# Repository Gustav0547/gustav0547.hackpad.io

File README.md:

# gustav0547.hackpad.io
# Jason's Hackpad

Macropad with 16 buttons, 15 to run shortcuts, 1 to swap between sets of keys, and a screen to display what set of keys is active.

## [Bottom Case](https://github.com/Gustav0547/gustav0547.hackpad.io/blob/4d3d6c4bc20b1932a387ed43a1a903aacc122e63/cad/Hackpad%20Case%20V1.step)

.png)
Bottom Case with PCB

Full Assembly

## [Top Case](https://github.com/Gustav0547/gustav0547.hackpad.io/blob/4d3d6c4bc20b1932a387ed43a1a903aacc122e63/cad/Hackpad%20Case%20Top%20V2.step)

.png)

## [PCB File](https://github.com/Gustav0547/gustav0547.hackpad.io/blob/4d3d6c4bc20b1932a387ed43a1a903aacc122e63/kicad/Jason's%20Hackpad.kicad_pcb)

.png)

## [Schematic](https://github.com/Gustav0547/gustav0547.hackpad.io/blob/4d3d6c4bc20b1932a387ed43a1a903aacc122e63/kicad/Jason's%20Hackpad.kicad_sch)

.png)

## Files
- Cad:
    - [Bottom Case](https://github.com/Gustav0547/gustav0547.hackpad.io/blob/main/cad/Hackpad%20Case%20V1.step)
    - [Top Case](https://github.com/Gustav0547/gustav0547.hackpad.io/blob/main/cad/Hackpad%20Case%20Top%20V2.step)
- KiCad:
    - [Schematic](https://github.com/Gustav0547/gustav0547.hackpad.io/blob/4d3d6c4bc20b1932a387ed43a1a903aacc122e63/kicad/Jason's%20Hackpad.kicad_sch)
    - [PCB File](https://github.com/Gustav0547/gustav0547.hackpad.io/blob/4d3d6c4bc20b1932a387ed43a1a903aacc122e63/kicad/Jason's%20Hackpad.kicad_pcb)
    - [PRL File](https://github.com/Gustav0547/gustav0547.hackpad.io/blob/4d3d6c4bc20b1932a387ed43a1a903aacc122e63/kicad/Jason's%20Hackpad.kicad_prl)
    - [PRO File](https://github.com/Gustav0547/gustav0547.hackpad.io/blob/4d3d6c4bc20b1932a387ed43a1a903aacc122e63/kicad/Jason's%20Hackpad.kicad_pro)

## [Bill of Materials](https://github.com/Gustav0547/gustav0547.hackpad.io/blob/8d4ffa0d519144a892c286018dd9fab355bb3349/kicad/Jason's%20Hackpad.csv)
- 16 1N4148 Diodes
- 16 MX Style Switches
- 16 Blank DSA Keycaps
- 1 Speeed XIAO RP2040
- 1 0.91" OLED Display
- 4 M3x16mm Screws
- 4 M3 Heatset Inserts

## Features
- 16 Buttons in a matrix
    - 15 for macro keys
    - 1 to switch sets of active macro keys
- 0.91" OLED Display to show active keyset
- Diodes to prevent ghosting
- XIAO-RP2040 microcontroller
- 3D printed enclosure

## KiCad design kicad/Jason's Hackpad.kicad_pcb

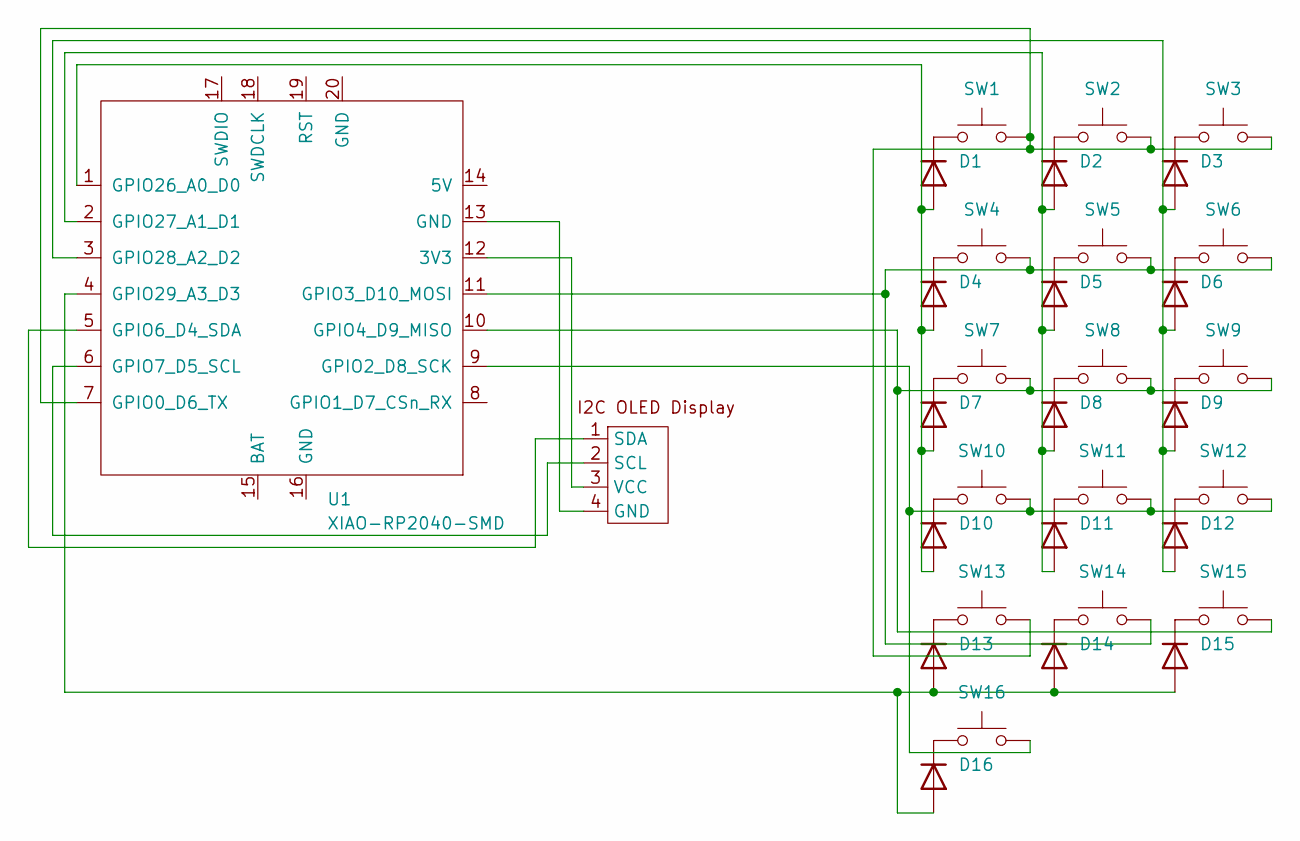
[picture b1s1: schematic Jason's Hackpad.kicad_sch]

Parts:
D1, D2, D3, D4, D5, D6, D7, D8, D9, D10, D11, D12, D13, D14, D15, D16: 1N4148; D_DO-35_SOD27_P7.62mm_Horizontal
SW1, SW2, SW3, SW4, SW5, SW6, SW7, SW8, SW9, SW10, SW11, SW12, SW13, SW14, SW15, SW16: SW_Push; SW_Cherry_MX_1.00u_PCB
U1: XIAO-RP2040-SMD; XIAO-RP2040-DIP
U2: Untitled

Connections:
unnamed: D1.2 (A), D4.2 (A), D7.2 (A), D10.2 (A), U1.1 (GPIO26_A0_D0)
unnamed: D1.1 (K), SW1.1
unnamed: D2.1 (K), SW2.1
unnamed: D3.1 (K), SW3.1
unnamed: D4.1 (K), SW4.1
unnamed: D5.1 (K), SW5.1
unnamed: D6.1 (K), SW6.1
unnamed: D7.1 (K), SW7.1
unnamed: D8.1 (K), SW8.1
unnamed: D9.1 (K), SW9.1
unnamed: D10.1 (K), SW10.1
unnamed: D2.2 (A), D5.2 (A), D8.2 (A), D11.2 (A), U1.2 (GPIO27_A1_D1)
unnamed: D11.1 (K), SW11.1
unnamed: D3.2 (A), D6.2 (A), D9.2 (A), D12.2 (A), U1.3 (GPIO28_A2_D2)
unnamed: D12.1 (K), SW12.1
unnamed: D13.2 (A), D14.2 (A), D15.2 (A), D16.2 (A), U1.4 (GPIO29_A3_D3)
unnamed: D13.1 (K), SW13.1
unnamed: D14.1 (K), SW14.1
unnamed: D15.1 (K), SW15.1
unnamed: D16.1 (K), SW16.1
unnamed: U1.12 (3V3), U2.3 (VCC)
unnamed: SW1.2, SW2.2, SW3.2, SW13.2, U1.7 (GPIO0_D6_TX)
unnamed: SW10.2, SW11.2, SW12.2, SW16.2, U1.9 (GPIO2_D8_SCK)
unnamed: SW4.2, SW5.2, SW6.2, SW14.2, U1.11 (GPIO3_D10_MOSI)
unnamed: SW7.2, SW8.2, SW9.2, SW15.2, U1.10 (GPIO4_D9_MISO)
unnamed: U1.5 (GPIO6_D4_SDA), U2.1 (SDA)
unnamed: U1.6 (GPIO7_D5_SCL), U2.2 (SCL)
unnamed: U1.13 (GND), U2.4 (GND)

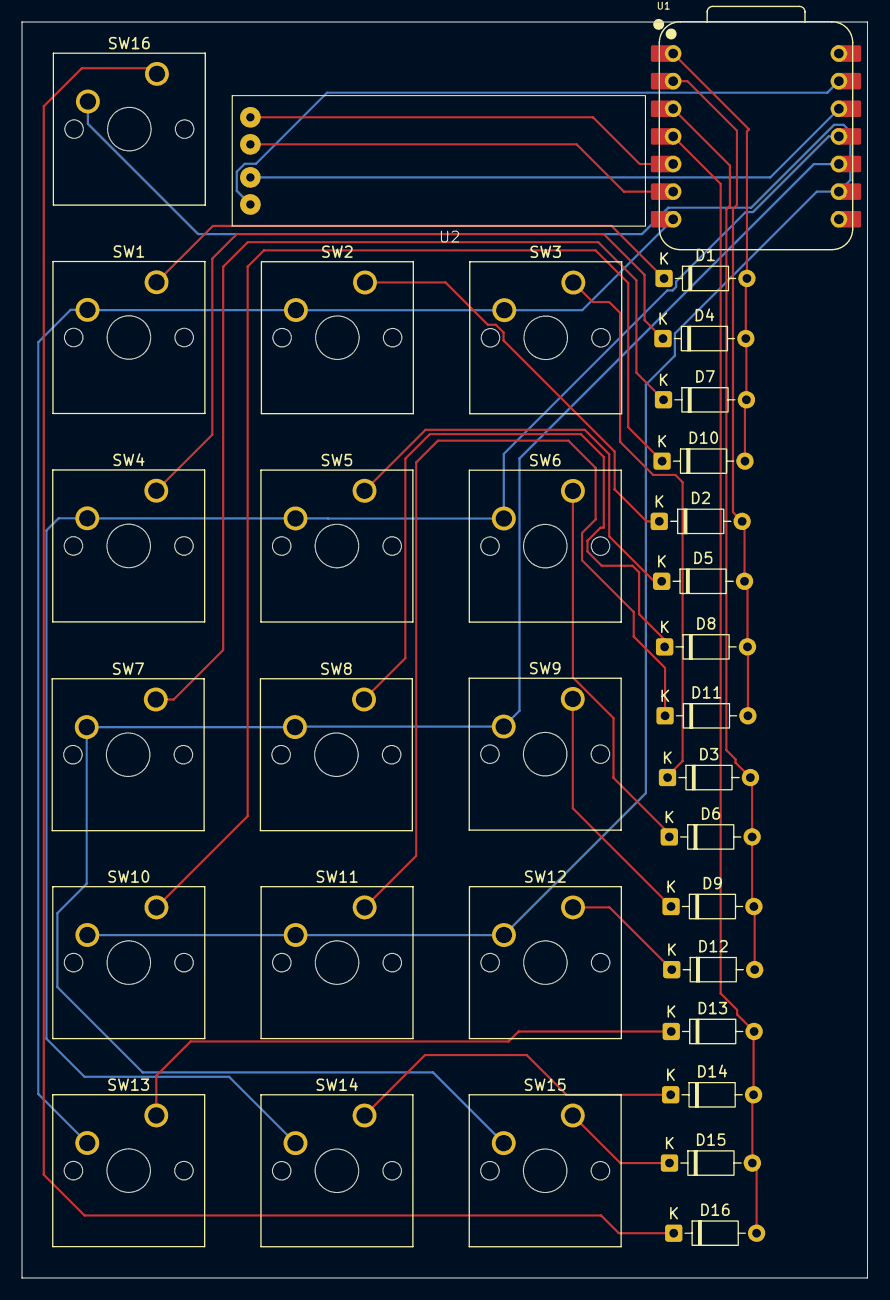
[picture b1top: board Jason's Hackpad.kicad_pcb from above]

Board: 2 copper layers, 77.8 x 115.5 mm, 34 parts (0 on the bottom side), 28 nets.

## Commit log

2025-11-30 Add files via upload
    Added screenshots of each file.
2025-12-01 Create cad
2025-12-01 Update and rename cad to ca
2025-12-01 Rename ca to cad/Hackpad Case Top V2.step
2025-12-01 Create hadf
2025-12-01 Create test
2026-01-04 Create firmware
